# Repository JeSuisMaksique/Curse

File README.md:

# Curse
Репозиторий курсового проекта
Описание датчика.
Датчик замеряет температуру/влажность и отправляет данные по Wi-Fi с помощью модуля ESP-01S. При нажатии на кнопку можно отобразить текущие показания на OLED дисплее.

Датчика включает:
1. Плату обработки;
2. Модуль ESP-01S;
3. OLED дисплей.

Функции платы обработки:
1. Периодический опрос датчика AHT20 по i2c и получение данных о температуре и влажности;
2. Передача полученных данных с помощью модуля ESP-01S;
3. Периодичский контроль заряда аккумулятора с помощью АЦП. При низком заряде аккумклятора датчик передаёт информацию о разряде аккумуляора по Wi-Fi с помощью ESP-01S.

Основную часть времени модуль ESP-01S находится в режие сна и активируется только для передачи данных

Плата обработки (v.0.1):

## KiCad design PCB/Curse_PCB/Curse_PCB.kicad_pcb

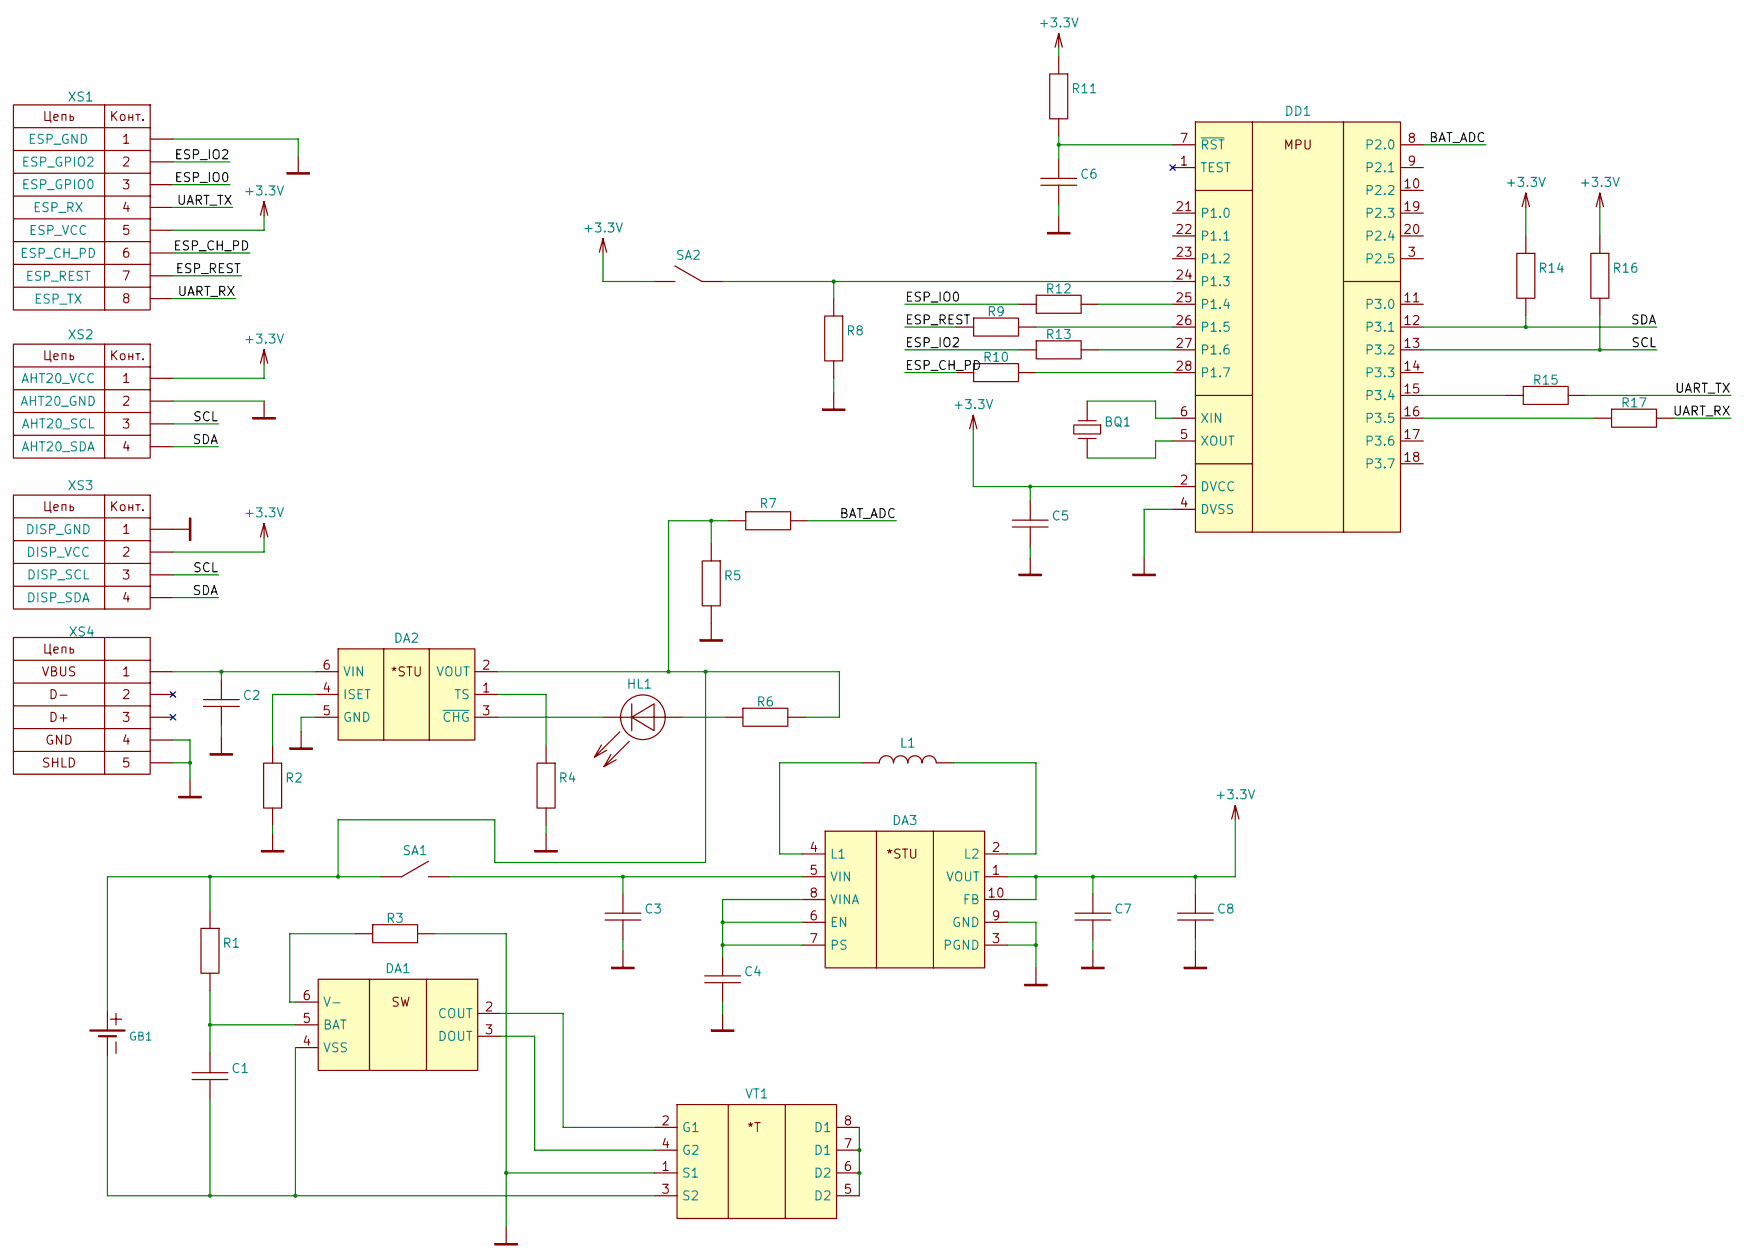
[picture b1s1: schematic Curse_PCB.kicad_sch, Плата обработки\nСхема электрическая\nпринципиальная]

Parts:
BQ1: 32.768 kHz 03215C2; Crystal_SMD_3215-2Pin_3.2x1.5mm
C1, C4, C5: 0.1 мкФ-NP0-50В ±5% 0603; C_0603_1608Metric
C2: 1 мкФ-NP0-16В ±5% 0805; C_0805_2012Metric
C3, C7, C8: 10 мкФ-NP0-16В ±5% 0805; C_0805_2012Metric
C6: 2200 пФ-NP0-50В ±5% 0603; C_0603_1608Metric
DA1: BQ29737 WSON-6; WSON-6_1.5x1.5mm_P0.5mm
DA2: BQ21040; SOT-23-6
DA3: TPS63031 WSON-10; WSON-10-1EP_2.5x2.5mm_P0.5mm_EP1.2x2mm_ThermalVias
DD1: MSP430F2112IPW TSSOP-28; TSSOP-28_4.4x9.7mm_P0.65mm
GB1: GB_BATTERY-KGL_Power
HL1: HL_LED; LED_0603_1608Metric
L1: VLS252010CX-1R5M-1 1,5 мкГн 2010; VLS252012CX
R1: 330 Ом ±5% 0603; R_0603_1608Metric
R2: 1,0 кОм ±1% 0603; R_0603_1608Metric
R3: 2,2 кОм ±5% 0603; R_0603_1608Metric
R4, R5, R7, R14, R16: 10 кОм ±5% 0603; R_0603_1608Metric
R6: 1,5 кОм ±5% 0603; R_0603_1608Metric
R8: 100 кОм ±5% 0603; R_0603_1608Metric
R9, R10, R12, R13, R15, R17: 510 Ом ±5% 0603; R_0603_1608Metric
R11: 47 кОм ±5% 0603; R_0603_1608Metric
SA1: PTS645VM58-2 LFS; SW_SPDT_PCM12
SA2: PTS645VM58-2 LFS; SW_Push_1P1T_NO_6x6mm_H9.5mm
VT1: BUK9K5R1-30E LFPAK56D; LFPAK56D
XS1: PBD-8; PinSocket_2x04_P2.54mm_Vertical_SMD
XS2, XS3: PBS-4; PinSocket_1x04_P2.54mm_Vertical
XS4: USB_A; USB_Micro-B_Molex_47346-0001

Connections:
+3.3V: C5.1, C7.1, C8.1, DA3.1 (VOUT), DA3.10 (FB), DD1.2 (DVCC), R11.1, R14.1, R16.1, SA2.2, XS1.5, XS2.1, XS3.2
/BAT_ADC: DD1.8 (P2.0), R7.2
/ESP_CH_PD: R10.1, XS1.6
/ESP_IO0: R12.1, XS1.3
/ESP_IO2: R13.1, XS1.2
/ESP_REST: R9.1, XS1.7
/SCL: DD1.13 (P3.2), R16.2, XS2.3, XS3.3
/SDA: DD1.12 (P3.1), R14.2, XS2.4, XS3.4
/UART_RX: R17.2, XS1.8
/UART_TX: R15.2, XS1.4
EXP: C2.2, C3.2, C4.2, C5.2, C6.2, C7.2, C8.2, DA2.5 (GND), DA3.3 (PGND), DA3.9 (GND), DA3.11 (EXP), DD1.4 (DVSS), R2.2, R3.2, R4.2, R5.2, R8.2, VT1.1 (S1), XS1.1, XS2.2, XS3.1, XS4.4, XS4.5
unnamed: BQ1.1, DD1.6 (XIN)
unnamed: BQ1.2, DD1.5 (XOUT)
unnamed: C1.1, DA1.5 (BAT), R1.2
unnamed: C1.2, DA1.4 (VSS), GB1.2, VT1.3 (S2)
unnamed: C2.1, DA2.6 (VIN), XS4.1
unnamed: C3.1, DA3.5 (VIN), SA1.2
unnamed: C4.1, DA3.6 (EN), DA3.7 (PS), DA3.8 (VINA)
unnamed: C6.1, DD1.7 (~RST), R11.2
unnamed: DA1.2 (COUT), VT1.2 (G1)
unnamed: DA1.3 (DOUT), VT1.4 (G2)
unnamed: DA1.6 (V-), R3.1
unnamed: DA2.1 (TS), R4.1
unnamed: DA2.2 (VOUT), GB1.1, R1.1, R5.1, R6.2, R7.1, SA1.1
unnamed: DA2.3 (~CHG), HL1.1 (K)
unnamed: DA2.4 (ISET), R2.1
unnamed: DA3.2 (L2), L1.2
unnamed: DA3.4 (L1), L1.1
unnamed: DD1.15 (P3.4), R15.1
unnamed: DD1.16 (P3.5), R17.1
unnamed: DD1.24 (P1.3), R8.1, SA2.1
unnamed: DD1.25 (P1.4), R12.2
unnamed: DD1.26 (P1.5), R9.2
unnamed: DD1.27 (P1.6), R13.2
unnamed: DD1.28 (P1.7), R10.2
unnamed: HL1.2 (A), R6.1
unnamed: VT1.5 (D2), VT1.6 (D2), VT1.7 (D1), VT1.8 (D1)

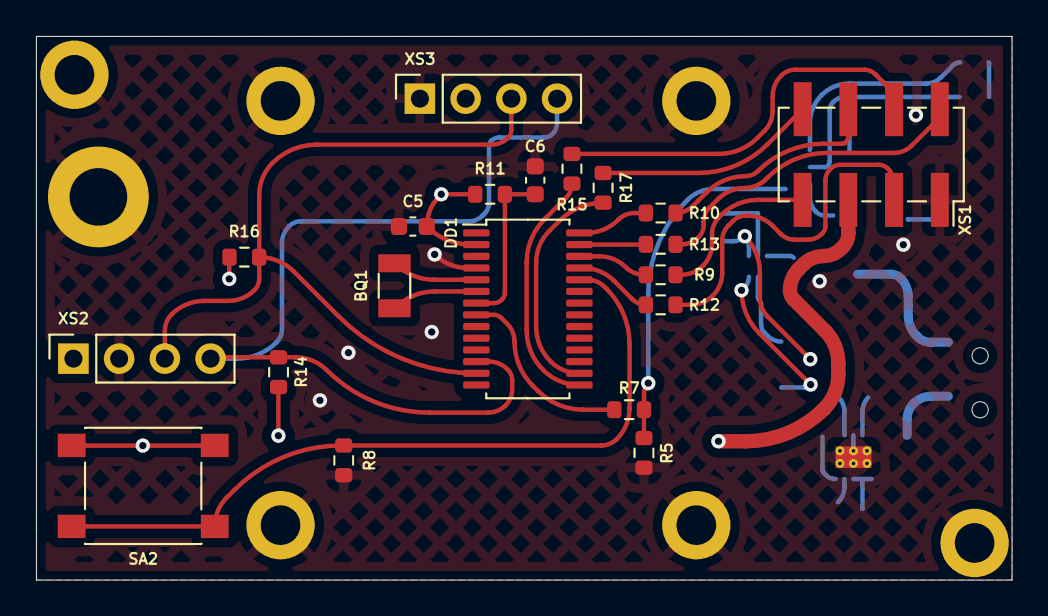
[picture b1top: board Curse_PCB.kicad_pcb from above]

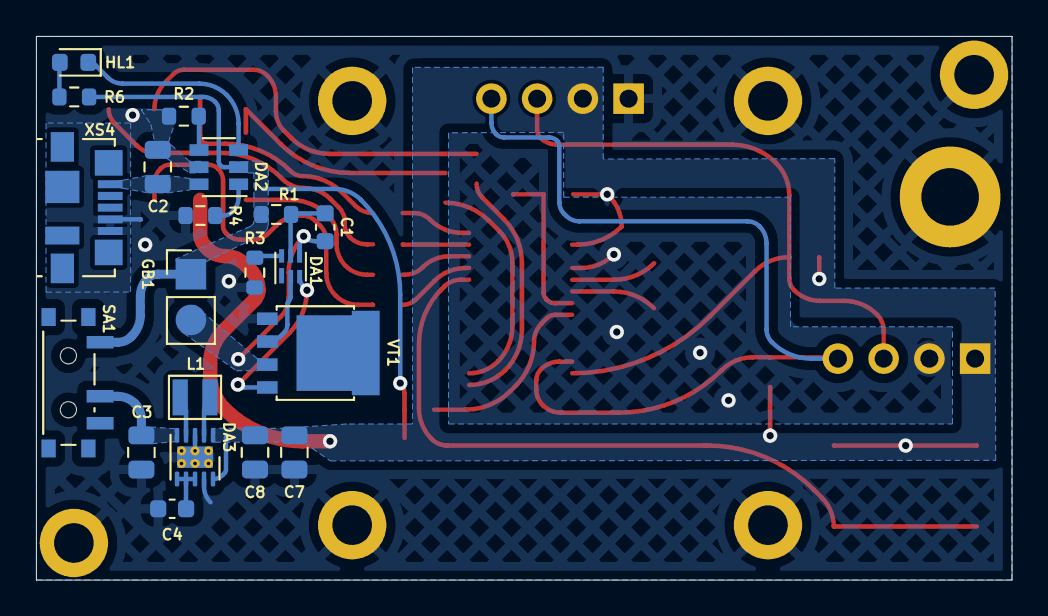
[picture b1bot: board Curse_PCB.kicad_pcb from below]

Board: 2 copper layers, 54.2 x 30.2 mm, 40 parts (20 on the bottom side), 36 nets.

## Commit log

2021-10-10 Initial
2021-10-11 SCH + PCB
2021-10-12 main.c
2021-10-12 Docs
2021-10-19 схема
2021-10-21 organization
2022-01-08 inventor
2022-01-10 pcb almost done
2022-01-10 сборка
2022-01-11 upd night
2022-01-12 almost done
2022-01-12 нужна структурная схема!!!
2022-01-13 ВСЁ!
2022-01-13 ФАСКИ
2022-01-14 исправления
2022-01-14 удалены файлы картинок
2022-01-14 чистка
2022-01-14 финал
